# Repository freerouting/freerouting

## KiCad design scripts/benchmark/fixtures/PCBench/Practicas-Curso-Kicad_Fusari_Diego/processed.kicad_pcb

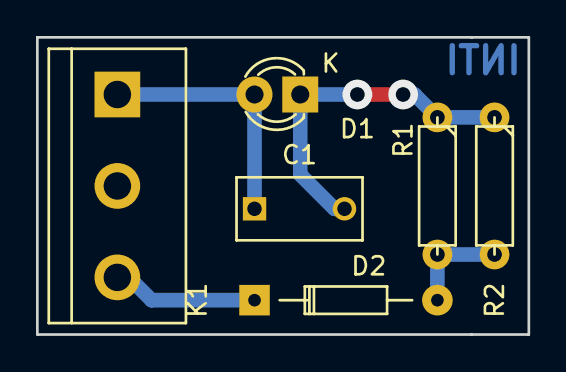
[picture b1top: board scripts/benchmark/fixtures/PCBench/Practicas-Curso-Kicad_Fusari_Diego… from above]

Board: 2 copper layers, 27.3 x 16.5 mm, 6 parts (0 on the bottom side), 4 nets.

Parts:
C1: 100nF; C_Rect_L7_W3.5_P5
D1: LED ROJO; LED-3MM
D2: 1N4148; Diode_DO-35_SOD27_Horizontal_RM10
K1: CONN_3; bornier3
R1, R2: 100K; R3-LARGE_PADS

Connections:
unnamed: C1.1, D1.2, K1.1
unnamed: C1.2, D1.1, R1.1, R2.1
unnamed: D2.1, K1.3
unnamed: D2.2, R1.2, R2.2

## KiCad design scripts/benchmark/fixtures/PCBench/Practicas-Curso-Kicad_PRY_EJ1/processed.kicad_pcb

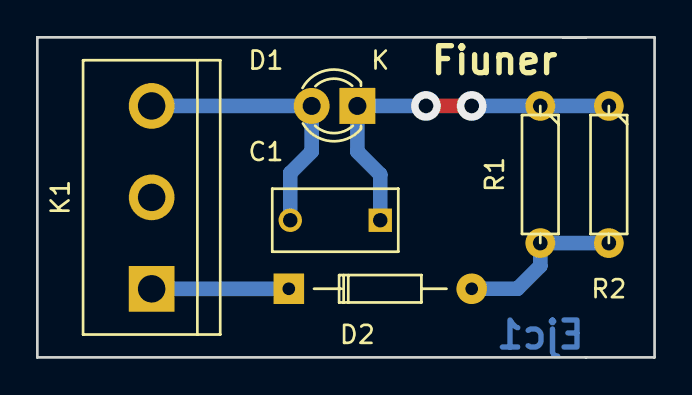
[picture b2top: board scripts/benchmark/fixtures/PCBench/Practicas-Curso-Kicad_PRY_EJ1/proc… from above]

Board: 2 copper layers, 34.3 x 17.8 mm, 6 parts (0 on the bottom side), 4 nets.

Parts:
C1: C; C_Rect_L7_W3.5_P5
D1: LED; LED-3MM
D2: D; Diode_DO-35_SOD27_Horizontal_RM10
K1: CONN_3; bornier3
R1: 100K; R3-LARGE_PADS
R2: 200K; R3-LARGE_PADS

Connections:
unnamed: C1.1, D1.1, R1.1, R2.1
unnamed: C1.2, D1.2, K1.3
unnamed: D2.1, K1.1
unnamed: D2.2, R1.2, R2.2
